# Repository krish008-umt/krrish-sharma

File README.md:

# krrish-sharma
int a=0;
if(a==0) :
print("zero")

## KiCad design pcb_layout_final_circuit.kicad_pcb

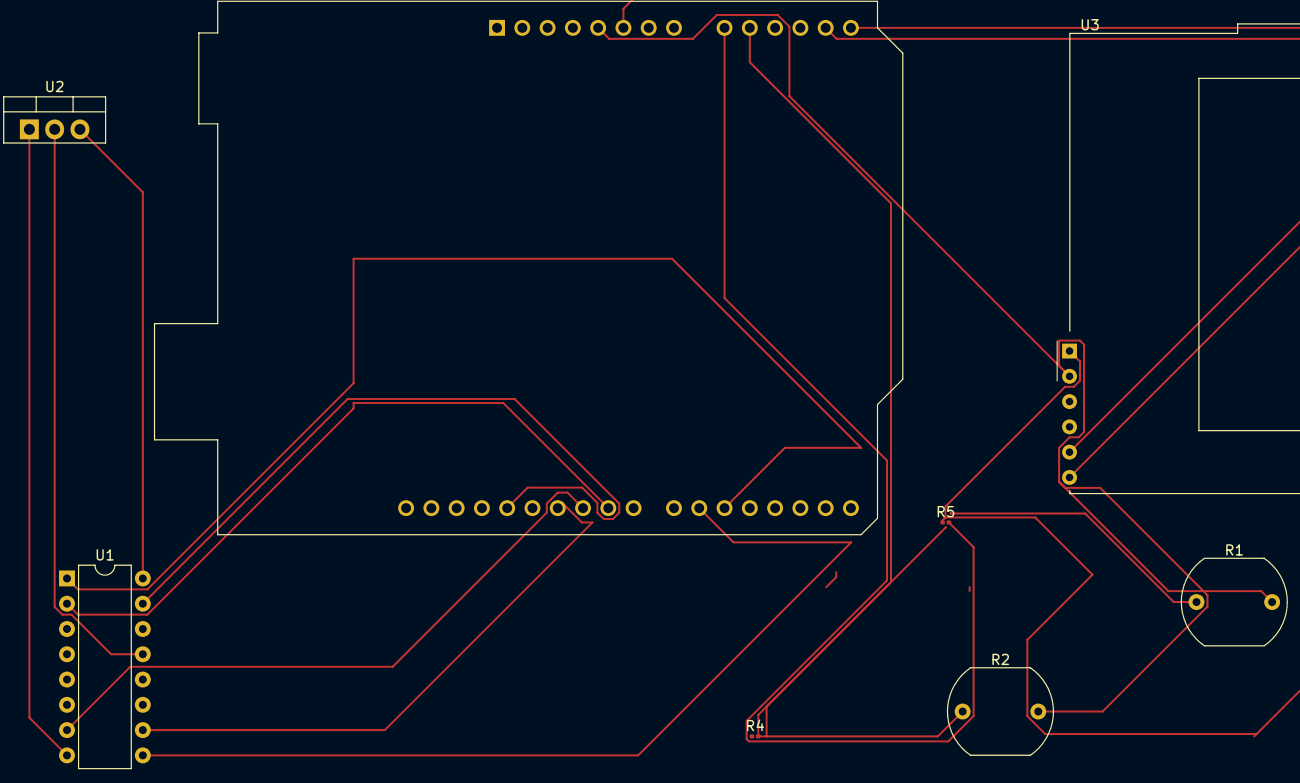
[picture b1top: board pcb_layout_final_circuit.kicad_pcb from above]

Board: 2 copper layers, 8 parts (0 on the bottom side), 17 nets.

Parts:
A1: Arduino_UNO_R3
R1, R2: LDR03; R_LDR_10x8.5mm_P7.6mm_Vertical
R4: 10K; R_0201_0603Metric
R5: 10k; R_0201_0603Metric
U1: L293D; DIP-16_W7.62mm
U2: LM7805_TO220; TO-220-3_Vertical
U3: EA_T123X-I2C

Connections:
unnamed: A1.5 (+5V), R1.2, R2.2, U3.2 (VDD)
unnamed: A1.9 (A0), R1.1, R5.2
unnamed: A1.10 (A1), R2.1, R4.2
unnamed: A1.20 (D5), U1.1 (EN1,2)
unnamed: A1.21 (D6), U1.9 (EN3,4)
unnamed: A1.24 (D9), U1.2 (1A)
unnamed: A1.25 (D10), U1.7 (2A)
unnamed: A1.26 (D11), U1.10 (3A)
unnamed: A1.28 (D13), U1.15 (4A)
unnamed: A1.2 (IOREF), A1.3 (~RESET)
unnamed: U1.4 (GND), U1.5 (GND)
unnamed: U1.16 (VCC1), U2.3 (VO)
unnamed: U1.8 (VCC2), U2.1 (VI)
unnamed: U1.12 (GND), U1.13 (GND), U2.2 (GND)
unnamed: A1.14 (SCL/A5), U3.6 (SCL)
unnamed: A1.13 (SDA/A4), U3.5 (SDA)
unnamed: A1.6 (GND), R4.1, R5.1, U3.1 (VSS)
